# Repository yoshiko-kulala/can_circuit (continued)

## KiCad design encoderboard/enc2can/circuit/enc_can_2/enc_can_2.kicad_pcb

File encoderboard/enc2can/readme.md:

# enc2can

エンコーダを読んでcanで送る基板とプログラム  

送信側はnucleo f303k8  
受信側はteensy3.2

トランシーバーはmcp2551  

canidは0x301(切り替えるdipを基板につけ忘れたので...)

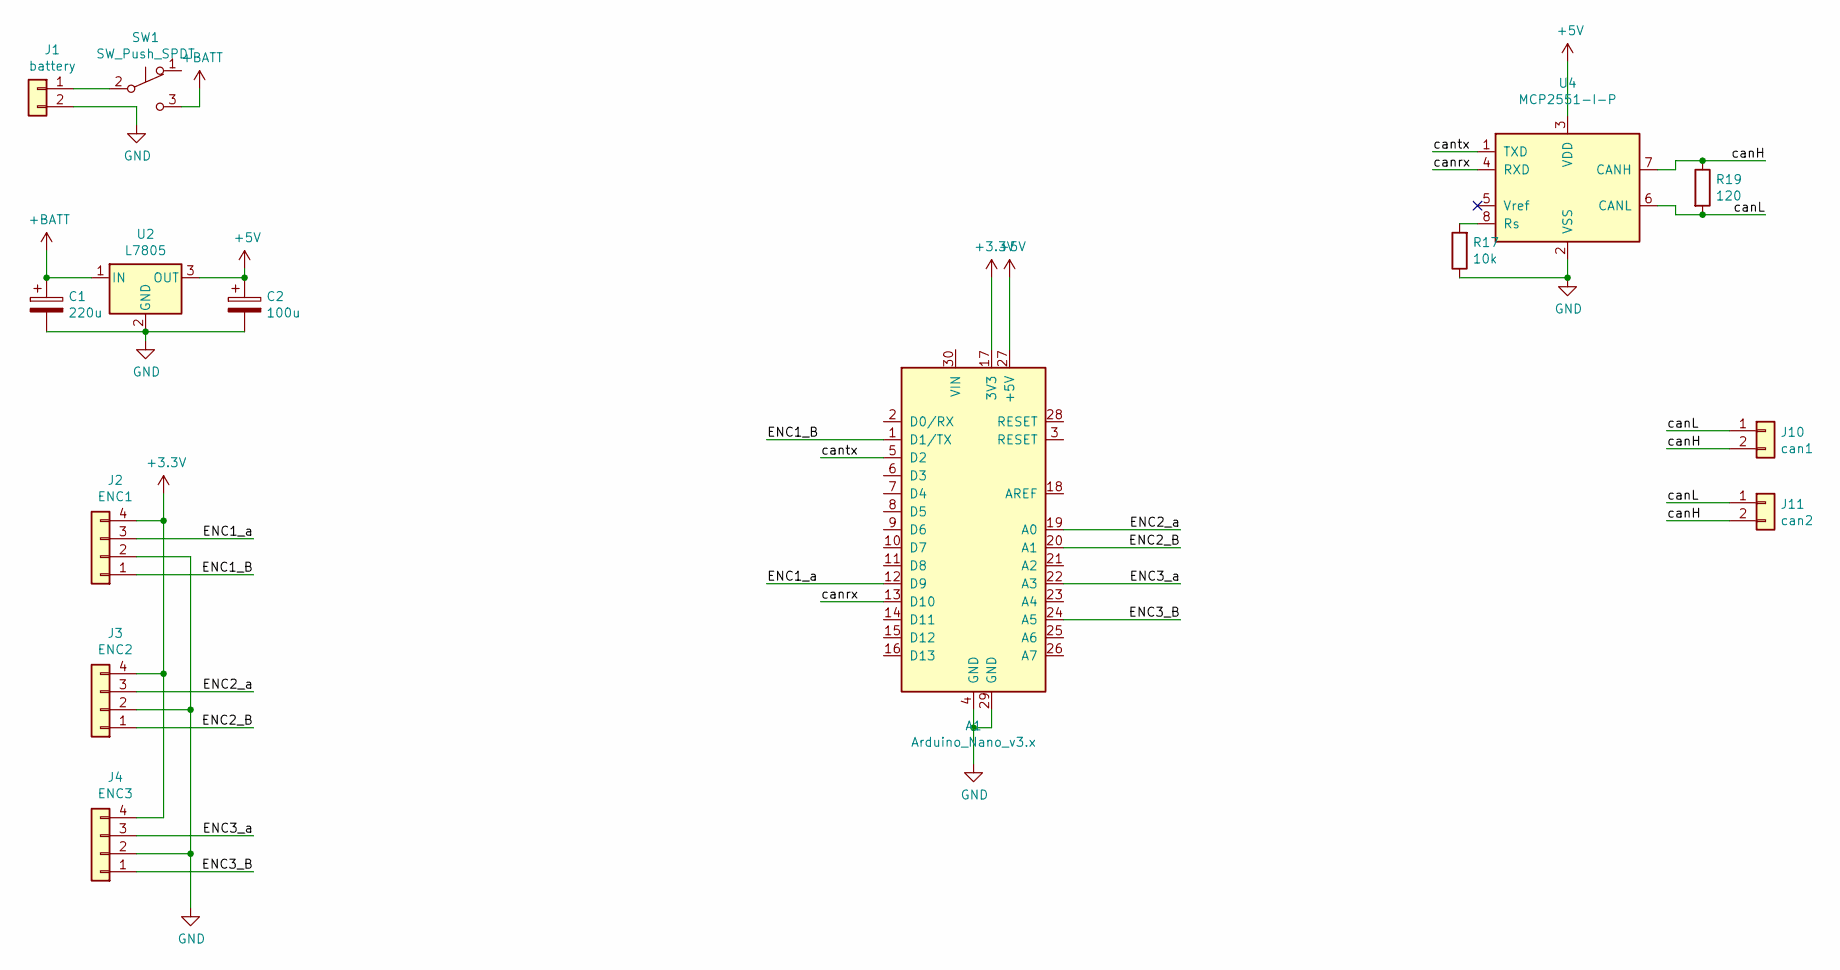
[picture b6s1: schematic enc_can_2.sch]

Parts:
A1: Arduino_Nano_v3.x; Arduino_Nano
C1: 220u; CP_Radial_D8.0mm_P2.50mm
C2: 100u; CP_Radial_D5.0mm_P2.00mm
J1: battery; JST_XH_B2B-XH-A_1x02_P2.50mm_Vertical
J2: ENC1; JST_XH_B4B-XH-A_1x04_P2.50mm_Vertical
J3: ENC2; JST_XH_B4B-XH-A_1x04_P2.50mm_Vertical
J4: ENC3; JST_XH_B4B-XH-A_1x04_P2.50mm_Vertical
J10: can1; JST_XH_B2B-XH-A_1x02_P2.50mm_Vertical
J11: can2; JST_XH_B2B-XH-A_1x02_P2.50mm_Vertical
R17: 10k; R_0603_1608Metric
R19: 120; R_0603_1608Metric
SW1: SW_Push_SPDT; mini_sw
U2: L7805; TO-252-2
U4: MCP2551-I-P; DIP-8_W7.62mm_Socket

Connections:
+3V3: A1.17 (3V3), J2.4, J3.4, J4.4
+5V: A1.27 (+5V), C2.1, U2.3 (OUT), U4.3 (VDD)
+BATT: C1.1, SW1.3 (C), U2.1 (IN)
/ENC1_B: A1.1 (D1/TX), J2.1
/ENC1_a: A1.12 (D9), J2.3
/ENC2_B: A1.20 (A1), J3.1
/ENC2_a: A1.19 (A0), J3.3
/ENC3_B: A1.24 (A5), J4.1
/ENC3_a: A1.22 (A3), J4.3
/canH: J10.2, J11.2, R19.1, U4.7 (CANH)
/canL: J10.1, J11.1, R19.2, U4.6 (CANL)
/canrx: A1.13 (D10), U4.4 (RXD)
/cantx: A1.5 (D2), U4.1 (TXD)
GND: A1.4 (GND), A1.29 (GND), C1.2, C2.2, J1.2, J2.2, J3.2, J4.2, R17.1, U2.2 (GND), U4.2 (VSS)
unnamed: J1.1, SW1.2 (B)
unnamed: R17.2, U4.8 (Rs)

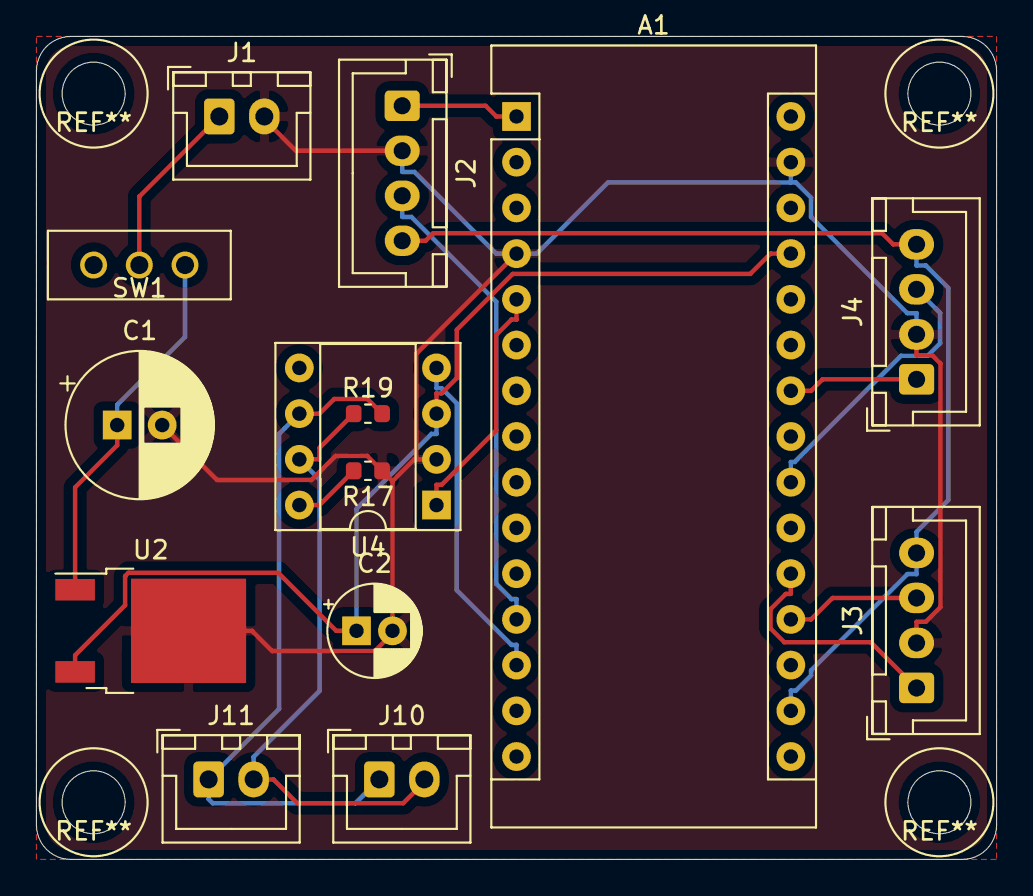
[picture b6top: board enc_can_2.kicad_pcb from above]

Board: 2 copper layers, 53.3 x 45.7 mm, 14 parts (0 on the bottom side), 16 nets.
